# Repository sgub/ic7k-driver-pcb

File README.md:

# Improved IC-7000 HF/VHF/UHF Transceiver driver stage PCB

## Features:
* Reduce pinheader spacing from 1.5mm to 1.27mm, for better availability of parts and easier mating with the PA board.
* Added resistor R103 in series with the gate of the MOSFET, to suppress self oscillication on certain conditions which could burn-off the driver module.

## BOM:
* Q504: ST Microelectronics PD55015-E 550MHz/15W MOSFET, PowerSO-10 Package, formed lead.
* R103: Choose a value by experiment from 1ohm (moderate damping) to 10ohm (~50% reduced final output power on UHF, but much safer), size 0805
* R102: 100ohm/1W, Axial_DIN0309_L9.0mm_D3.2mm_P15.24mm. Size is critical due to limited installation space.
* J107,J104,J103,J102,J101: PinHeader_1x04_P1.27mm_Vertical, 11mm total height.
* C102: 39pF/100V, Size 1206.
* C101: 10nF/50V, size 0805.

## Build notes:
* Prefered board material is FR4 double layer, 1.6mm thick.
* Apply enough solder between the underside of the MOSFET and the heatsink for effective heat conducting, avoid space, soldering/heating with proper tool. Refer STMicroelectronics AN1294 Application note for temperature limit and technique recommendation.

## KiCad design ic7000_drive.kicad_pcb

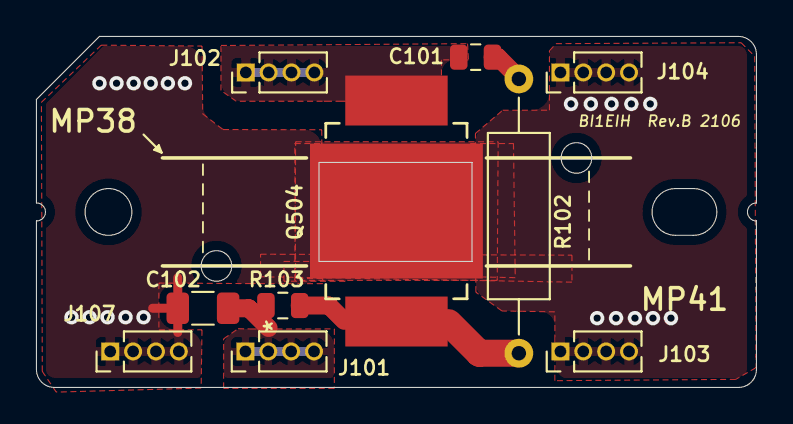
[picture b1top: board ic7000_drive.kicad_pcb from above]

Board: 2 copper layers, 40.0 x 19.5 mm, 10 parts (0 on the bottom side), 5 nets.

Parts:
C101: 0.1µF; C_0805_2012Metric
C102: 39p; C_1206_3216Metric
J101, J102, J103, J104, J107: Conn_01x04; PinHeader_1x04_P1.27mm_Vertical
Q504: PD55015-E; PD55008-E
R102: 100R/1W; R_Axial_DIN0309_L9.0mm_D3.2mm_P15.24mm_Horizontal
R103: 100R*; R_0805_2012Metric

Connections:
GND: C102.2, J103.1, J103.2, J103.3, J103.4, J104.1, J104.2, J104.3, J104.4, J107.1, J107.2, J107.3, J107.4, Q504.EPAD
unnamed: C101.1, R102.2
unnamed: C101.2, J102.1, J102.2, J102.3, J102.4, Q504.2
unnamed: C102.1, J101.1, J101.2, J101.3, J101.4, R103.1
unnamed: Q504.1, R102.1, R103.2

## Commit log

2021-02-02 modified: README.md
2021-02-02 new file: gerber/ic7000_drive-B_Cu.gbr new file: gerber/ic7000_drive-B_Mask.gbr new file: gerber/ic7000_drive-B_Paste.gbr new file: gerber/ic7000_drive-B_SilkS.gbr new file: gerber/ic7000_drive-Edge_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
2021-02-03 Add C101 size.

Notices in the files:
ic7000_drive.kicad_pcb:
CC BY 4.0
parts and their libraries:
Copyright 2016 Accelerated Designs. All rights reserved.
